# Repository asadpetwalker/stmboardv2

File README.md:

# stmboardv2

# What it is and why I made it
Initially, this was a standard better stm dev board, but as I progressed with this project, I realized I didn't want to do the exact same thing I did last time, so I added sensors and wireless capabilities, a speaker and more interfacing options, for extra security layers. Additionally, I added an ESP32 to sideload tasks, to add another programming option, and to add a microSD card peripheral to store more memory on my board. I made it because the STM is an extremely powerful chip, and my last board didn't do it justice from the lack of capabilities and GPIO, as well as the lack of indication leds and in general less than apt design. Thus, I spent much more time integrating multiple sensors and features, adding indicator LEDs and in general making it much more powerful and useful than a just a simple dev board.

# Assembly Instructions
1. Solder

# Pictures

# Bill of Materials

| LCSC#     | MPN                 | Manufacturer              | Package         | Description                                                                                             |   Quantity |   Total Price ($) | Product Link                                               |
|:----------|:--------------------|:--------------------------|:----------------|:--------------------------------------------------------------------------------------------------------|-----------:|------------------:|:-----------------------------------------------------------|
| C29936    | CL10B105KA8NNNC     | Samsung Electro-Mechanics | 0603            | 1uF ±10% 25V Ceramic Capacitor X7R 0603                                                                 |         20 |              0.43 | [Link](https://www.lcsc.com/product-detail/C29936.html)    |
| C1705     | CL10A475KP8NNNC     | Samsung Electro-Mechanics | 0603            | 4.7uF ±10% 10V Ceramic Capacitor X5R 0603                                                               |         50 |              1    | [Link](https://www.lcsc.com/product-detail/C1705.html)     |
| C13738    | X322516MLB4SI       | YXC Crystal Oscillators   | SMD3225-4P      | Crystal 16MHz ±10ppm 9pF SMD3225-4P                                                                     |          5 |              0.47 | [Link](https://www.lcsc.com/product-detail/C13738.html)    |
| C164170   | 472192001           | MOLEX                     | SMD             | Micro SD card (TF card) Connector and Ejector Hinged Lid Surface Mount                                  |          1 |              0.73 | [Link](https://www.lcsc.com/product-detail/C164170.html)   |
| C2933084  | FRC0402F2702TS      | FOJAN                     | 0402            | 27kΩ ±1% 62.5mW 0402 Thick Film Resistor                                                                |        100 |              0.19 | [Link](https://www.lcsc.com/product-detail/C2933084.html)  |
| C2909342  | FRC0402F2700TS      | FOJAN                     | 0402            | 270Ω ±1% 62.5mW 0402 Thick Film Resistor                                                                |        100 |              0.25 | [Link](https://www.lcsc.com/product-detail/C2909342.html)  |
| C1550542  | CP2102N-A02-GQFN20  | SILICON LABS              | QFN-20-EP(3x3)  | USB to UART 3Mbps QFN-20-EP(3x3) Controllers RoHS                                                       |          1 |              2.29 | [Link](https://www.lcsc.com/product-detail/C1550542.html)  |
| C5656610  | ICS-43434           | TDK InvenSense            | LGA-6(3.5x2.7)  | Omnidirectional -26dB 64dB LGA-6(3.5x2.7) Microphones RoHS                                              |          1 |              4.13 | [Link](https://www.lcsc.com/product-detail/C5656610.html)  |
| C94355    | STM32F411RET6       | ST                        | LQFP-64(10x10)  | ARM Cortex-M4 32 Bit 100MHz LQFP-64(10x10) Microcontrollers RoHS                                        |          1 |              6.87 | [Link](https://www.lcsc.com/product-detail/C94355.html)    |
| C2913198  | ESP32-S3-WROOM-1-N8 | ESPRESSIF                 | SMD,25.5x18mm   | 2.4GHz ESP32-S3 Chip On-board PCB Antenna -98.2dBm SMD,25.5x18mm RF Transceiver Modules and Modems RoHS |          1 |              4.91 | [Link](https://www.lcsc.com/product-detail/C2913198.html)  |
| C22365428 | AP2112K-1.8TRG1(MS) | MSKSEMI                   | SOT-23-5        | Linear Voltage Regulator IC Positive Fixed 1 Output 600mA SOT-23-5                                      |          5 |              0.48 | [Link](https://www.lcsc.com/product-detail/C22365428.html) |
| C726001   | ICM-20948           | TDK InvenSense            | QFN-24(3x3)     | QFN-24(3x3) IMUs (Inertial Measurement Units) RoHS                                                      |          1 |             18.96 | [Link](https://www.lcsc.com/product-detail/C726001.html)   |
| C22469962 | TXB0102DCT(LX)      | lingxingic                | TSSOP-8         | 45Mbps 1 2 TSSOP-8 Translators, Level Shifters                                                          |          5 |              1.25 | [Link](https://www.lcsc.com/product-detail/C22469962.html) |
| C910544   | MAX98357AETE+T      | MAXIM                     | TQFN-16-EP(3x3) | 2.4mA 2.5V~5.5V 3.2Wx1@4Ω Class D TQFN-16-EP(3x3) Audio Amplifiers RoHS                                 |          1 |              1.32 | [Link](https://www.lcsc.com/product-detail/C910544.html)   |
| C880859   | 0603N9R0C500CT      | Walsin                    | 0603            | 9pF 50V Ceramic Capacitor NP0 0603                                                                      |         50 |              0.45 | [Link](https://www.lcsc.com/product-detail/C880859.html)   |
| -         | Custom PCB          | JLCPCB                    | -               | Custom printed circuit board                                                                            |          5 |              8.34 | -                                                          |
| -         | Shipping            | -                         | -               | Shipping cost                                                                                           |          1 |             18    | -                                                          |

**Total Estimated Cost:** $70.07

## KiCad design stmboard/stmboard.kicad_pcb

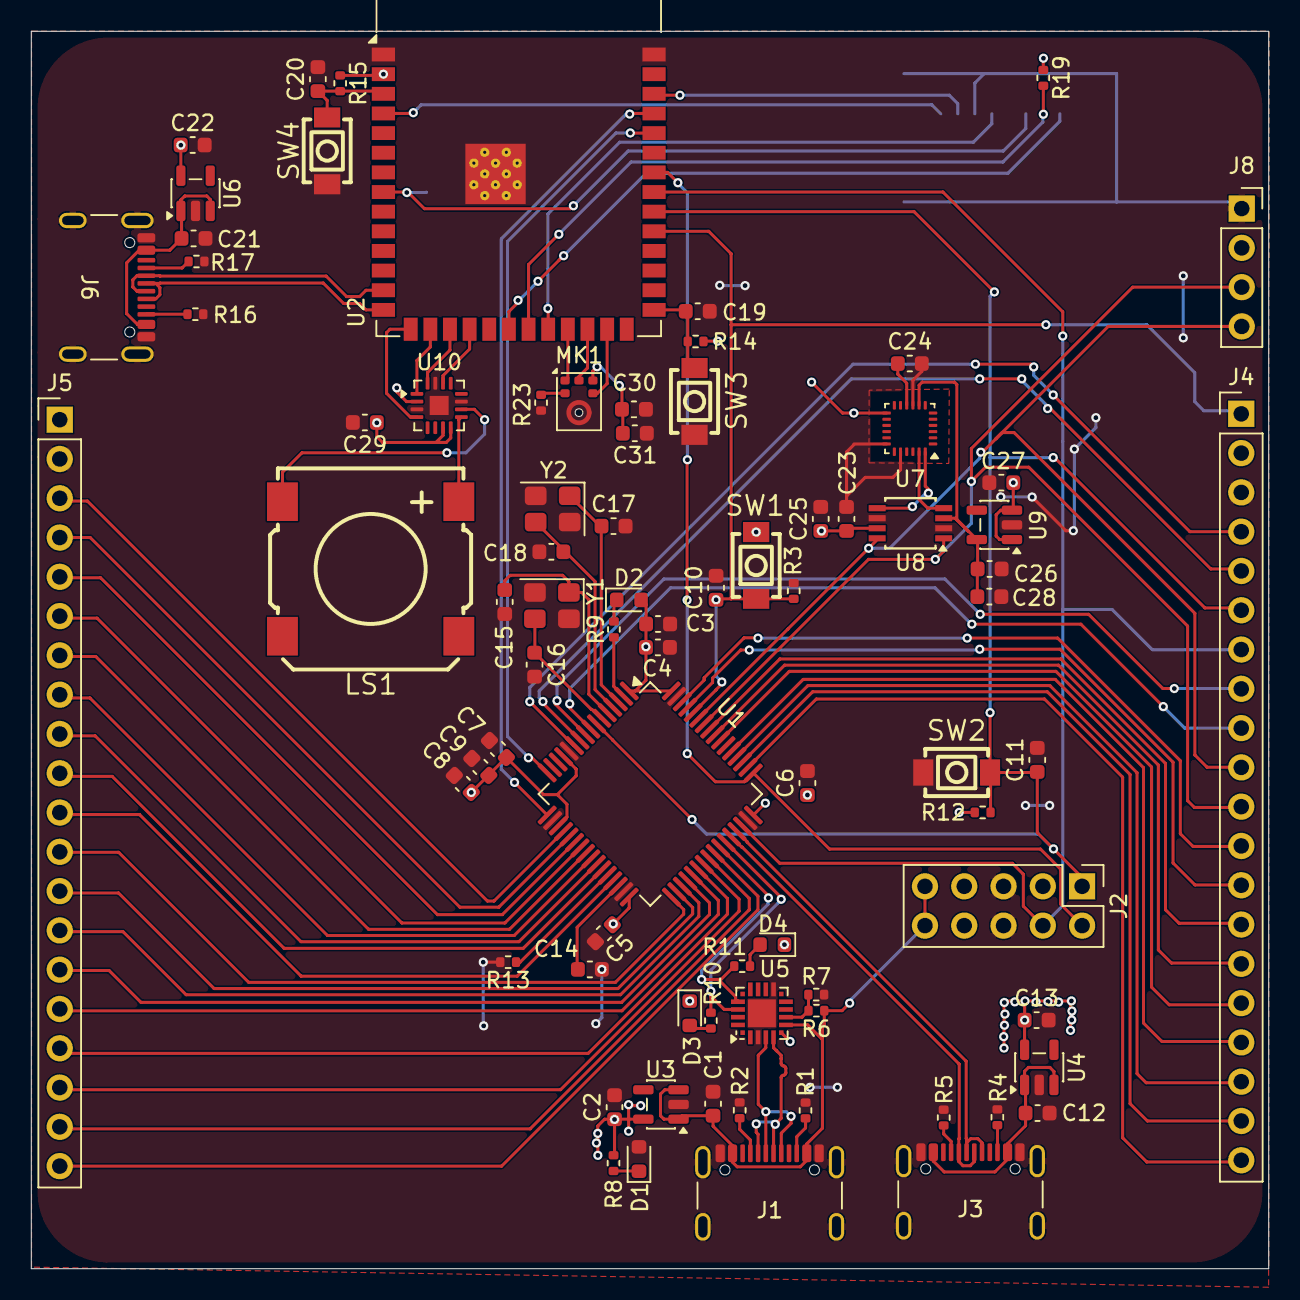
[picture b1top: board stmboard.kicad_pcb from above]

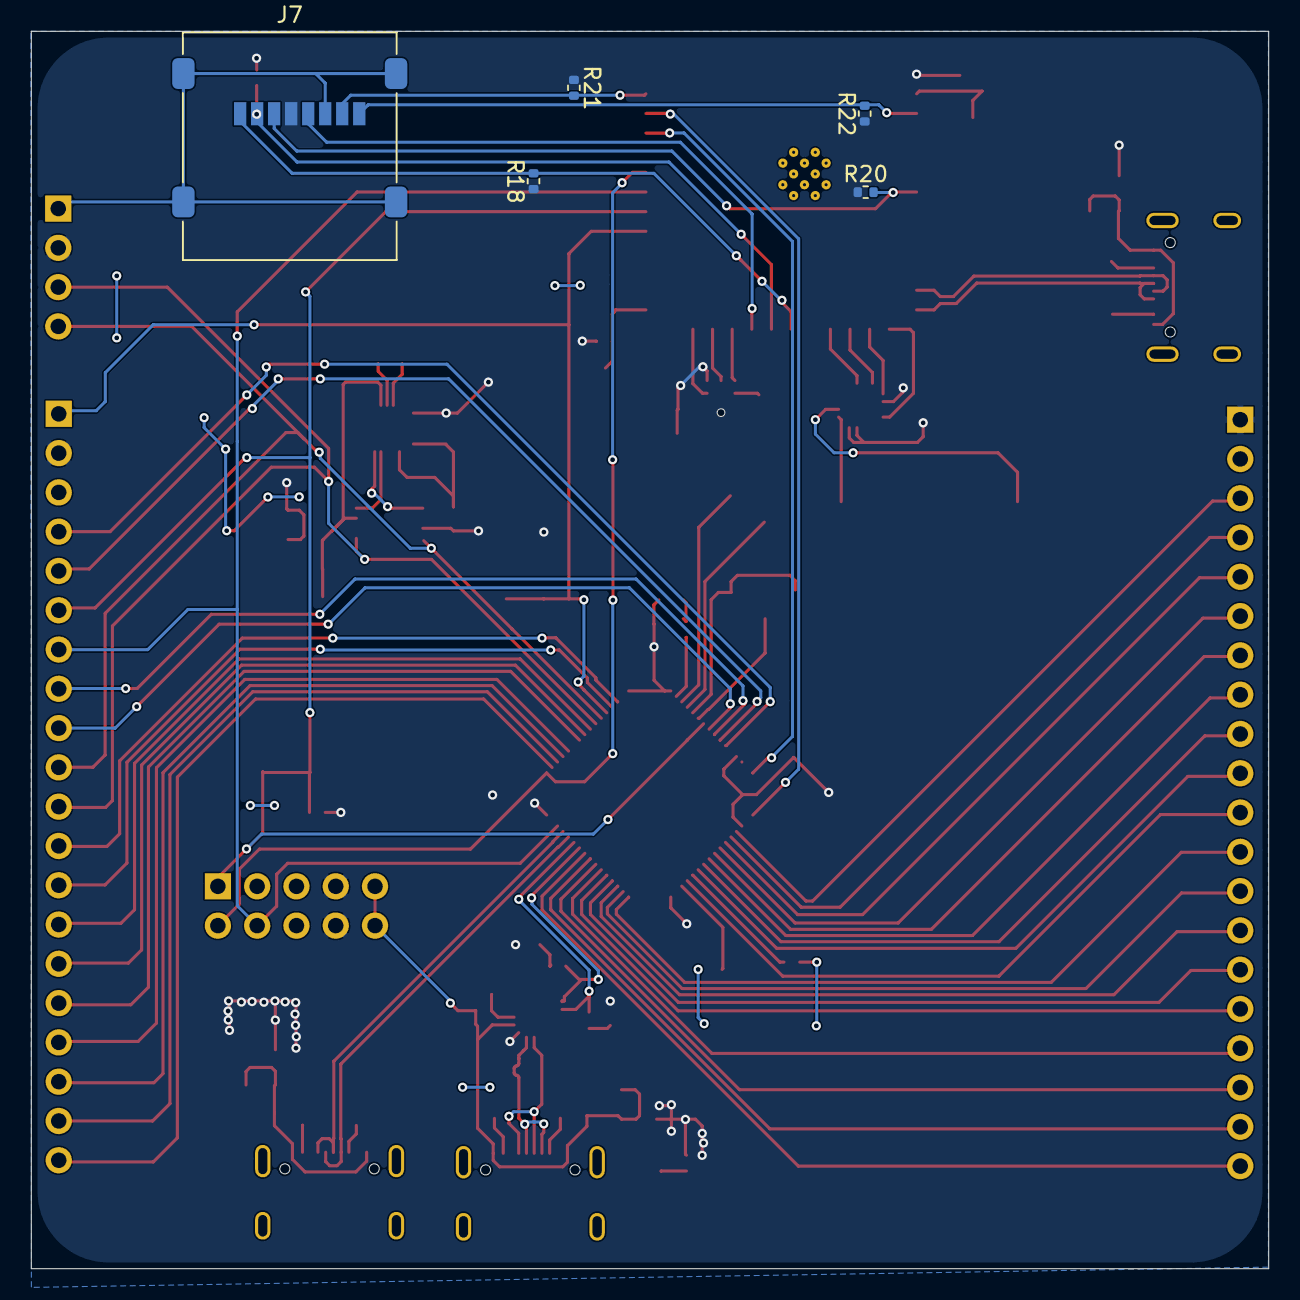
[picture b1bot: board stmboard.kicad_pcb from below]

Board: 2 copper layers, 80.0 x 80.0 mm, 84 parts (5 on the bottom side), 92 nets.

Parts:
C1, C2, C9, C12, C13, C21, C22, C27, C28: 1u; C_0603_1608Metric
C3, C4, C5, C6, C7, C10, C11, C14, C19, C20, C23, C24, C25, C26, C29, C30, C31: 100n; C_0603_1608Metric
C8: 4.7u; C_0603_1608Metric
C15, C16, C17, C18: 18p; C_0603_1608Metric
D1, D2: LED; LED_0603_1608Metric
D3: TX; LED_0603_1608Metric
D4: RX; LED_0603_1608Metric
J1, J3, J6: USB_C_Receptacle_USB2.0_14P; USB_C_Receptacle_GCT_USB4105-xx-A_16P_TopMnt_Horizontal
J2: Conn_02x05_Odd_Even; PinHeader_2x05_P2.54mm_Vertical
J4, J5: Conn_01x20_Socket; PinHeader_1x20_P2.54mm_Vertical
J7: Micro_SD_Card; microSD_HC_Molex_47219-2001
J8: Conn_01x04; PinSocket_1x04_P2.54mm_Vertical
LS1: Speaker; BUZ-SMD_4P-L13.0-W13.0-P11.4-BL
MK1: SPH0645LM4H; Knowles_SPH0645LM4H-6_3.5x2.65mm
R1, R2, R4, R5, R16, R17: 5.1k; R_0402_1005Metric
R3, R7, R12, R13, R14, R15, R18, R19, R20, R21, R22, R23: 10k; R_0402_1005Metric
R6: 27k; R_0402_1005Metric
R8, R9: 1k; R_0402_1005Metric
R10, R11: 270; R_0402_1005Metric
SW1: BOOT0; KEY-SMD_L4.0-W3.0-LS4.9-1
SW2: NRST; KEY-SMD_L4.0-W3.0-LS4.9-1
SW3, SW4: BOOT; KEY-SMD_L4.0-W3.0-LS4.9-1
U1: STM32F411RCTx; LQFP-64_10x10mm_P0.5mm
U2: ESP32-S3-WROOM-1
U3, U4, U6: AP2112K-3.3; SOT-23-5
U5: CP2102N-Axx-xQFN20; SiliconLabs_QFN-20-1EP_3x3mm_P0.5mm_EP1.8x1.8mm
U7: ICM-20948; InvenSense_QFN-24_3x3mm_P0.4mm
U8: TXB0102DCT; TSSOP-8_3x3mm_P0.65mm
U9: AP2112K-1.8; SOT-23-5
U10: MAX98357A; TQFN-16-1EP_3x3mm_P0.5mm_EP1.23x1.23mm
Y1: 25MHz; Crystal_SMD_Abracon_ABM8G-4Pin_3.2x2.5mm
Y2: 32.768KHz; Crystal_SMD_Abracon_ABM8G-4Pin_3.2x2.5mm

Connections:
+1V8: C26.1, C28.1, U7.8 (VDDIO), U8.3 (VCCA), U9.5 (VOUT)
+3V3: C2.1, C3.1, C4.1, C5.1, C6.1, C7.1, C8.1, C9.1, C13.1, C22.1, C23.1, C25.1, C27.1, C29.1, C30.1, C31.1, D2.2 (A), D3.1 (K), D4.1 (K), J2.7, J2.8, J4.2, J5.1, J7.4 (VDD), J8.2, MK1.5 (VDD), R8.1, R12.1, R14.1, R15.1, R18.1, R19.1, R20.1, R21.1, R22.1, SW1.2, U1.1 (VBAT), U1.13 (VDDA), U1.19 (VDD), U1.32 (VDD), U1.48 (VDD), U1.64 (VDD), U2.2 (3V3), U3.5 (VOUT), U4.5 (VOUT), U5.6 (VDD), U6.5 (VOUT), U7.13 (VDD), U8.7 (VCCB), U9.1 (VIN), U9.3 (EN), U10.2 (GAIN_SLOT), U10.7 (VDD), U10.8 (VDD)
/BCLK: U2.17 (IO9), U10.16 (BCLK)
/BCLK2: MK1.4 (BCLK), U2.25 (IO48)
/BOOT0: C10.1, J4.1, R3.1, SW1.1, U1.60 (BOOT0), U2.31 (IO38)
/CLK: J7.5 (CLK), U2.22 (IO14)
/CMD: J7.3 (CMD), R20.2, U2.8 (IO15)
/D+: J3.A6 (D+), J3.B6 (D+), U1.45 (PA12)
/D-: J3.A7 (D-), J3.B7 (D-), U1.44 (PA11)
/DAT0: J7.7 (DAT0), R21.2, U2.38 (IO2)
/DAT1: J7.8 (DAT1), R22.2, U2.4 (IO4)
/DAT2: J7.1 (DAT2), R18.2, U2.20 (IO12)
/DAT3: J7.2 (DAT3/CD), R19.2, U2.21 (IO13)
/DATA: MK1.6 (DATA), U2.24 (IO47)
/DIN: U2.16 (IO46), U10.1 (DIN)
/D_{0}+: J1.A6 (D+), J1.B6 (D+), U5.4 (D+)
/D_{0}-: J1.A7 (D-), J1.B7 (D-), U5.5 (D-)
/D_{1}+: J6.A6 (D+), J6.B6 (D+), U2.14 (USB_D+)
/D_{1}-: J6.A7 (D-), J6.B7 (D-), U2.13 (USB_D-)
/FCLK: U2.18 (IO10), U10.14 (LRCLK)
/NRST: C11.1, J2.1, J4.6, R12.2, SW2.1, U1.7 (NRST), U2.32 (IO39)
/OSC_{IN}: C15.1, U1.5 (PH0), Y1.1
/OSC_{OUT}: C16.1, U1.6 (PH1), Y1.3
/PA4: J5.3, U1.20 (PA4)
/PA5: J5.4, U1.21 (PA5)
/PA6: J5.5, U1.22 (PA6)
/PA7: J5.6, U1.23 (PA7)
/PA8: J5.20, U1.41 (PA8)
/PA15: J4.20, U1.50 (PA15)
/PB0: J5.9, U1.26 (PB0)
/PB1: J5.10, U1.27 (PB1)
/PB2: R13.1, U1.28 (PB2)
/PB3: J4.16, U1.55 (PB3)
/PB4: J4.15, U1.56 (PB4)
/PB5: J4.14, U1.57 (PB5)
/PB6: J4.11, J8.3, U1.58 (PB6), U8.1 (B2)
/PB7: J4.10, J8.4, U1.59 (PB7), U8.8 (B1)
/PB8: J4.13, U1.61 (PB8)
/PB9: J4.12, U1.62 (PB9)
/PB10: J5.11, U1.29 (PB10)
/PB12: J5.12, U1.33 (PB12)
/PB13: J5.13, U1.34 (PB13)
/PB14: J5.15, U1.36 (PB15)
/PB15: J5.14, U1.35 (PB14)
/PC0: J4.9, U1.8 (PC0)
/PC1: J4.8, U1.9 (PC1)
/PC2: J4.5, U1.10 (PC2)
/PC3: J4.4, U1.11 (PC3)
/PC4: J5.7, U1.24 (PC4)
/PC5: J5.8, U1.25 (PC5)
/PC6: J5.16, U1.37 (PC6)
/PC7: J5.17, U1.38 (PC7)
/PC8: J5.18, U1.39 (PC8)
/PC9: J5.19, U1.40 (PC9)
/PC10: J4.19, U1.51 (PC10)
/PC11: J4.18, U1.52 (PC11)
/PC12: J4.17, U1.53 (PC12)
/PC13: R9.1, U1.2 (PC13)
/PC14: C17.1, U1.3 (PC14), Y2.1
/PC15: C18.1, U1.4 (PC15), Y2.3
/RX: R11.1, U1.42 (PA9), U5.17 (RXD)
/RX1: U1.17 (PA3), U2.37 (TXD0)
/SCL_{1V8}: U7.23 (SCL/SCLK), U8.4 (A2)
/SDA_{1V8}: U7.24 (SDA/SDI), U8.5 (A1)
/SWCLK: J2.2, U1.49 (PA14), U2.34 (IO41)
/SWDIO: J2.4, J4.7, U1.46 (PA13), U2.33 (IO40)
/TX: R10.1, U1.43 (PA10), U5.18 (TXD)
/TX1: U1.16 (PA2), U2.36 (RXD0)
/VBUS: C1.1, J1.A4 (VBUS), J1.A9 (VBUS), J1.B4 (VBUS), J1.B9 (VBUS), J2.9, J2.10, R6.1, U3.1 (VIN), U3.3 (EN), U5.7 (VREGIN)
/WS: MK1.1 (WS), U2.23 (IO21)
/~SD_MODE: U2.15 (IO3), U10.4 (~SD_MODE)
GND: C1.2, C2.2, C3.2, C4.2, C5.2, C6.2, C7.2, C8.2, C9.2, C10.2, C11.2, C12.2, C13.2, C14.2, C15.2, C16.2, C17.2, C18.2, C19.2, C20.2, C21.2, C22.2, C23.2, C24.2, C25.2, C26.2, C27.2, C28.2, C29.2, C30.2, C31.2, D1.2 (A), J1.A1 (GND), J1.A12 (GND), J1.B1 (GND), J1.B12 (GND), J1.SH (SHIELD), J2.5, J2.6, J3.A1 (GND), J3.A12 (GND), J3.B1 (GND), J3.B12 (GND), J3.SH (SHIELD), J4.3, J5.2, J6.A1 (GND), J6.A12 (GND), J6.B1 (GND), J6.B12 (GND), J6.SH (SHIELD), J7.6 (VSS), J7.SH (SHIELD), J8.1, MK1.3 (GND), R1.2, R2.1, R3.2, R4.2, R5.1, R7.2, R13.2, R16.2, R17.1, R23.2, SW2.2, SW3.1, SW4.1, U1.12 (VSSA), U1.18 (VSS), U1.31 (VSS), U1.47 (VSS), U1.63 (VSS), U2.1 (GND), U2.40 (GND), U2.41 (GND), U3.2 (GND), U4.2 (GND), U5.3 (GND), U5.12 (GND), U5.21 (GND), U6.2 (GND), U7.9 (SDO/AD0), U7.18 (GND), U7.20 (GND), U8.2 (GND), U8.6 (OE), U9.2 (GND), U10.3 (GND), U10.11 (GND), U10.15 (GND), U10.17 (PAD), Y1.2 (G), Y1.4 (G), Y2.2 (G), Y2.4 (G)
unnamed: D1.1 (K), R8.2
unnamed: D2.1 (K), R9.2
unnamed: D3.2 (A), R10.2
unnamed: D4.2 (A), R11.2
unnamed: J1.A5 (CC1), R2.2
unnamed: J1.B5 (CC2), R1.1
unnamed: J3.A5 (CC1), R5.2
unnamed: J3.B5 (CC2), R4.1
unnamed: J6.A5 (CC1), R17.2
unnamed: J6.B5 (CC2), R16.1
unnamed: MK1.2 (SEL), R23.1
unnamed: C14.1, U1.30 (VCAP1)
unnamed: C20.1, R15.2, SW4.2, U2.3 (EN)
unnamed: C19.1, R14.2, SW3.2, U2.27 (IO0)
unnamed: C12.1, J3.A4 (VBUS), J3.A9 (VBUS), J3.B4 (VBUS), J3.B9 (VBUS), U4.1 (VIN), U4.3 (EN)
unnamed: R6.2, R7.1, U5.8 (VBUS)
unnamed: C21.1, J6.A4 (VBUS), J6.A9 (VBUS), J6.B4 (VBUS), J6.B9 (VBUS), U6.1 (VIN), U6.3 (EN)
unnamed: C24.1, U7.10 (REGOUT)
unnamed: LS1.2, U10.10 (OUTN)
unnamed: LS1.1, U10.9 (OUTP)
